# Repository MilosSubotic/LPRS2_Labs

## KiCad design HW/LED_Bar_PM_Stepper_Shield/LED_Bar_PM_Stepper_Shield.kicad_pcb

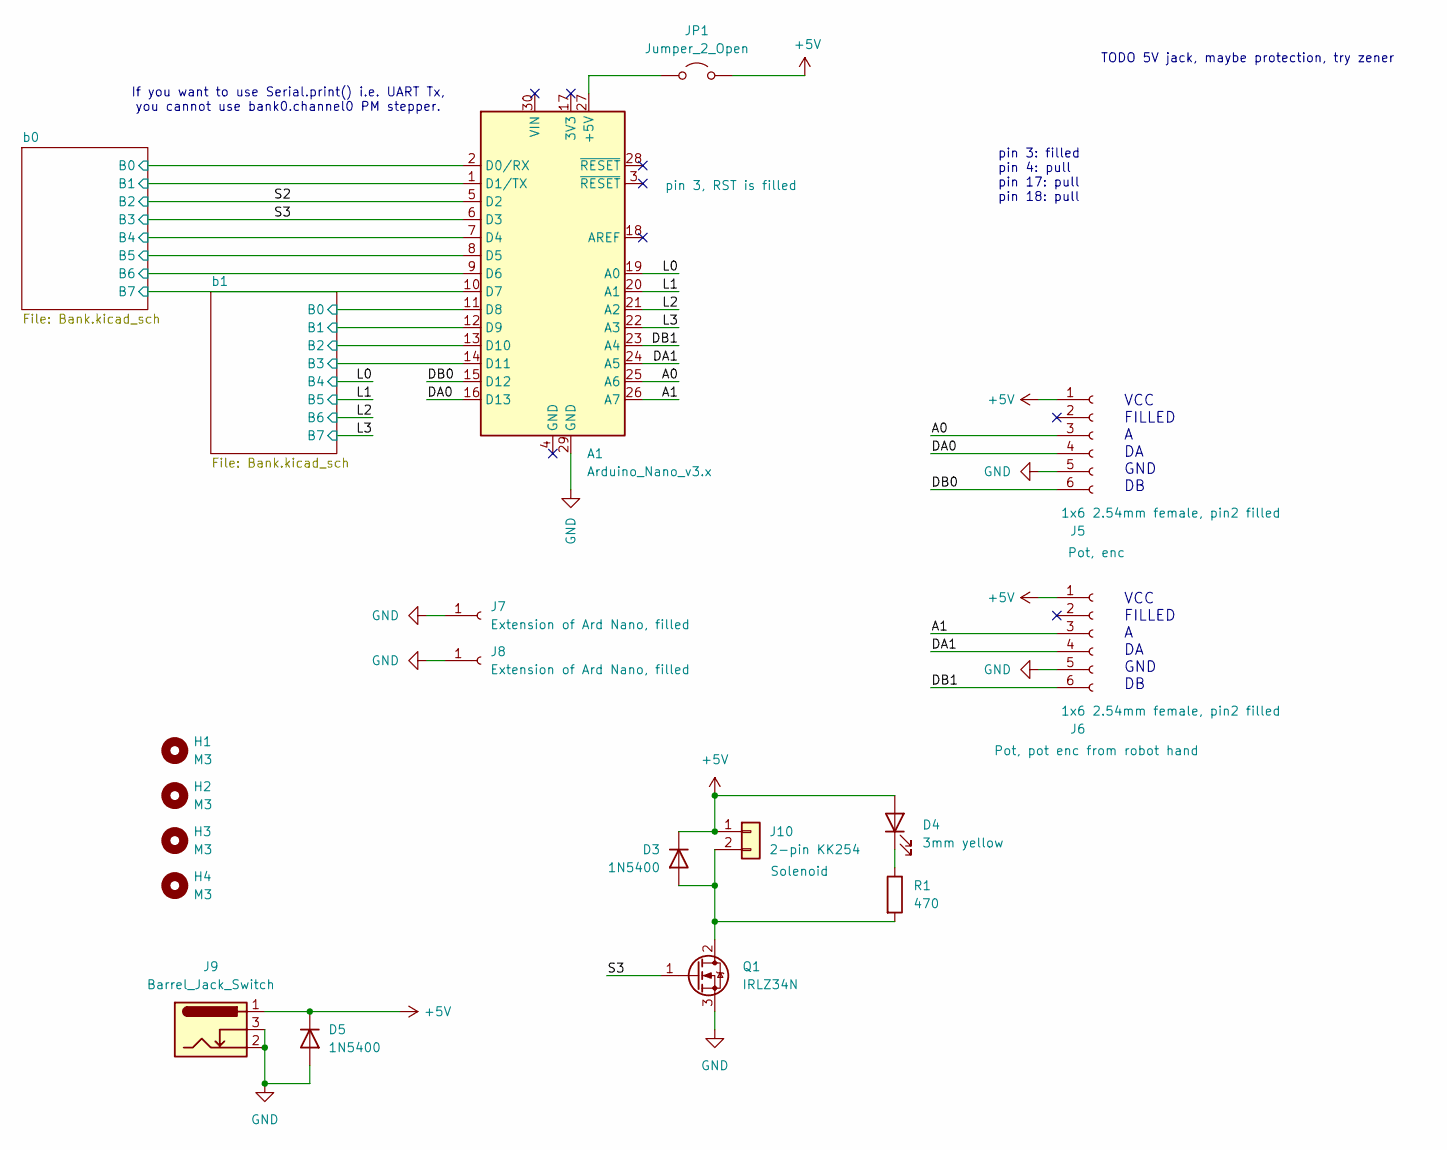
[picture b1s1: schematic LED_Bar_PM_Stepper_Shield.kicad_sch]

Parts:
A1: Arduino_Nano_v3.x; Arduino_Nano
D3, D5: 1N5400; D_DO-201AD_P5.08mm_Vertical_AnodeUp
D4: 3mm yellow; LED_D3.0mm_Pinf
H1, H2, H3, H4: M3; MountingHole_3.2mm_M3
J5, J6: 1x6 2.54mm female, pin2 filled; PinHeader_1x06_P2.54mm_Vertical
J7, J8: Extension of Ard Nano, filled; PinSocket_1x01_P2.54mm_Vertical
J9: Barrel_Jack_Switch; BarrelJack_Horizontal
J10: 2-pin KK254; Molex_KK-254_AE-6410-02A_1x02_P2.54mm_Vertical
JP1: Jumper_2_Open; PinHeader_1x02_P2.54mm_Vertical
Q1: IRLZ34N; TO-220-3_Vertical
R1: 470; R_Axial_DIN0207_L6.3mm_D2.5mm_P7.62mm_Horizontal

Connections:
+5V: D3.1 (K), D4.2 (A), D5.1 (K), J5.1, J6.1, J9.1, J10.1, JP1.2 (B); also elsewhere on the board
/A0: A1.25 (A6), J5.3
/A1: A1.26 (A7), J6.3
/DA0: A1.16 (D13), J5.4
/DA1: A1.24 (A5), J6.4
/DB0: A1.15 (D12), J5.6
/DB1: A1.23 (A4), J6.6
/L0: A1.19 (A0); also elsewhere on the board
/L1: A1.20 (A1); also elsewhere on the board
/L2: A1.21 (A2); also elsewhere on the board
/L3: A1.22 (A3); also elsewhere on the board
/S2: A1.5 (D2); also elsewhere on the board
/S3: A1.6 (D3), Q1.1 (G); also elsewhere on the board
/b0/B0: A1.2 (D0/RX); also elsewhere on the board
/b0/B1: A1.1 (D1/TX); also elsewhere on the board
/b0/B4: A1.7 (D4); also elsewhere on the board
/b0/B5: A1.8 (D5); also elsewhere on the board
/b0/B6: A1.9 (D6); also elsewhere on the board
/b0/B7: A1.10 (D7); also elsewhere on the board
/b1/B0: A1.11 (D8); also elsewhere on the board
/b1/B1: A1.12 (D9); also elsewhere on the board
/b1/B2: A1.13 (D10); also elsewhere on the board
/b1/B3: A1.14 (D11); also elsewhere on the board
GND: A1.29 (GND), D5.2 (A), J5.5, J6.5, J7.1, J8.1, J9.2, J9.3, Q1.3 (S); also elsewhere on the board
unnamed: A1.27 (+5V), JP1.1 (A)
unnamed: D3.2 (A), J10.2, Q1.2 (D), R1.2
unnamed: D4.1 (K), R1.1

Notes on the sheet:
If you want to use Serial.print() i.e. UART Tx, you cannot use bank0.channel0 PM stepper.
VCC FILLED A DA GND DB
TODO 5V jack, maybe protection, try zener
pin 3: filled pin 4: pull pin 17: pull pin 18: pull

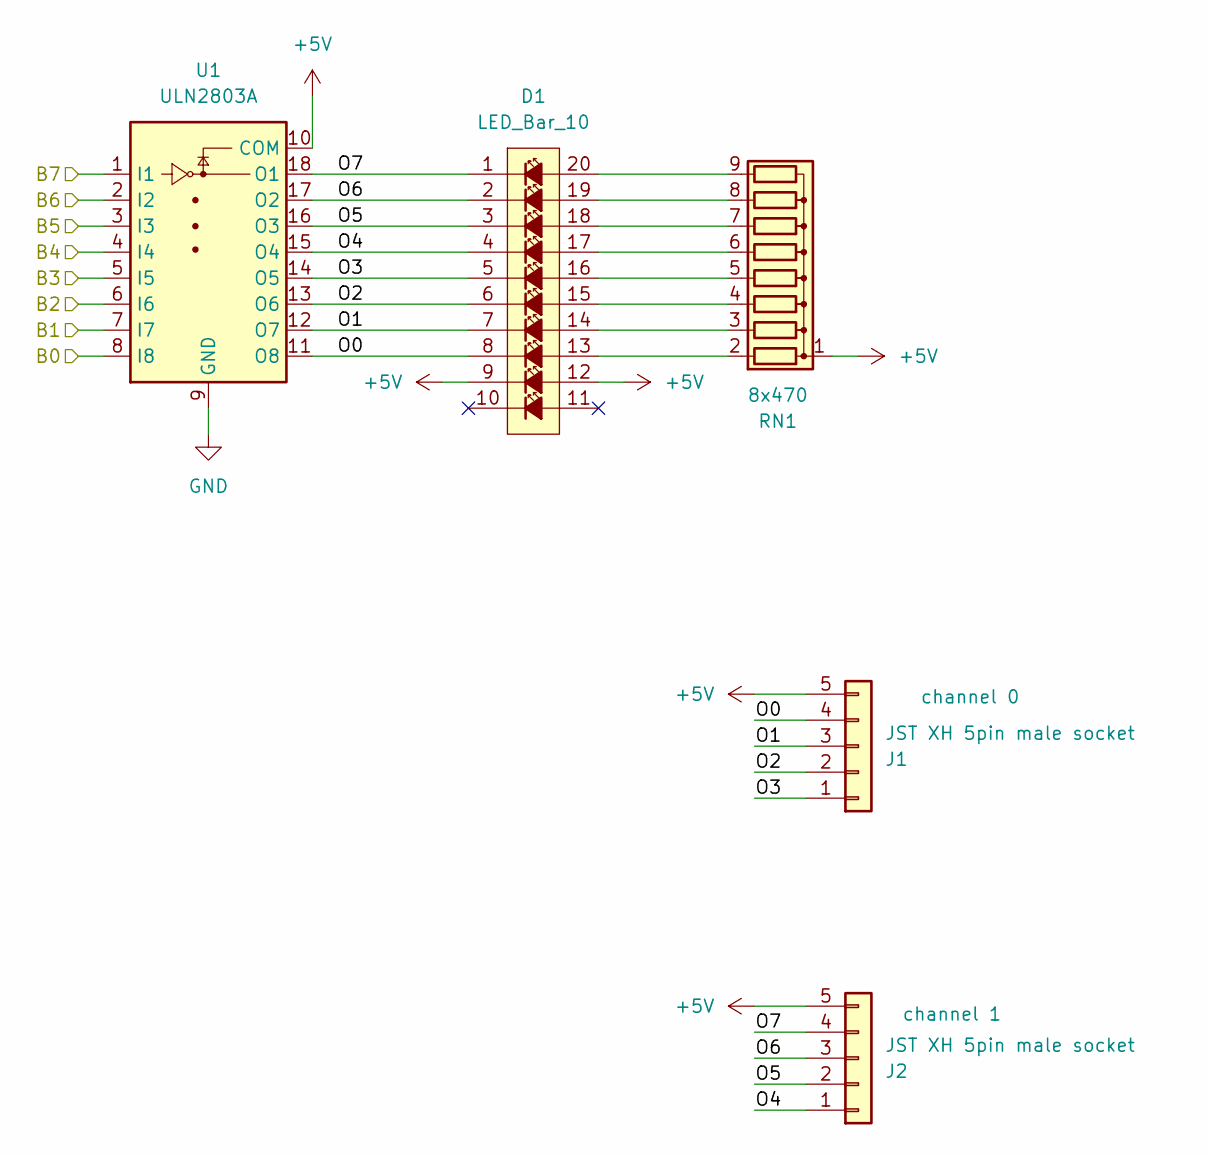
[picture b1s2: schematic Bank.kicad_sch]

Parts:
D1: LED_Bar_10; DIP-20_W7.62mm_Socket
J1, J2: JST XH 5pin male socket; JST_XH_B5B-XH-A_1x05_P2.50mm_Vertical
RN1: 8x470; R_Array_SIP9
U1: ULN2803A; DIP-18_W7.62mm_Socket

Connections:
+5V: D1.9, D1.12, J1.5, J2.5, RN1.1 (common), U1.10 (COM); also elsewhere on the board
/S2: U1.6 (I6); also elsewhere on the board
/S3: U1.5 (I5); also elsewhere on the board
/b0/B0: U1.8 (I8); also elsewhere on the board
/b0/B1: U1.7 (I7); also elsewhere on the board
/b0/B4: U1.4 (I4); also elsewhere on the board
/b0/B5: U1.3 (I3); also elsewhere on the board
/b0/B6: U1.2 (I2); also elsewhere on the board
/b0/B7: U1.1 (I1); also elsewhere on the board
/b0/O0: D1.8, J1.4, U1.11 (O8)
/b0/O1: D1.7, J1.3, U1.12 (O7)
/b0/O2: D1.6, J1.2, U1.13 (O6)
/b0/O3: D1.5, J1.1, U1.14 (O5)
/b0/O4: D1.4, J2.1, U1.15 (O4)
/b0/O5: D1.3, J2.2, U1.16 (O3)
/b0/O6: D1.2, J2.3, U1.17 (O2)
/b0/O7: D1.1, J2.4, U1.18 (O1)
GND: U1.9 (GND); also elsewhere on the board
unnamed: D1.13, RN1.2 (R1)
unnamed: D1.14, RN1.3 (R2)
unnamed: D1.15, RN1.4 (R3)
unnamed: D1.16, RN1.5 (R4)
unnamed: D1.17, RN1.6 (R5)
unnamed: D1.18, RN1.7 (R6)
unnamed: D1.19, RN1.8 (R7)
unnamed: D1.20, RN1.9 (R8)

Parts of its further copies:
D2: LED_Bar_10; DIP-20_W7.62mm_Socket
J3, J4: JST XH 5pin male socket; JST_XH_B5B-XH-A_1x05_P2.50mm_Vertical
RN2: 8x470; R_Array_SIP9
U2: ULN2803A; DIP-18_W7.62mm_Socket

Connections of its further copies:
+5V: D2.9, D2.12, J3.5, J4.5, RN2.1 (common), U2.10 (COM); also elsewhere on the board
/L0: U2.4 (I4); also elsewhere on the board
/L1: U2.3 (I3); also elsewhere on the board
/L2: U2.2 (I2); also elsewhere on the board
/L3: U2.1 (I1); also elsewhere on the board
/b1/B0: U2.8 (I8); also elsewhere on the board
/b1/B1: U2.7 (I7); also elsewhere on the board
/b1/B2: U2.6 (I6); also elsewhere on the board
/b1/B3: U2.5 (I5); also elsewhere on the board
/b1/O0: D2.8, J3.4, U2.11 (O8)
/b1/O1: D2.7, J3.3, U2.12 (O7)
/b1/O2: D2.6, J3.2, U2.13 (O6)
/b1/O3: D2.5, J3.1, U2.14 (O5)
/b1/O4: D2.4, J4.1, U2.15 (O4)
/b1/O5: D2.3, J4.2, U2.16 (O3)
/b1/O6: D2.2, J4.3, U2.17 (O2)
/b1/O7: D2.1, J4.4, U2.18 (O1)
GND: U2.9 (GND); also elsewhere on the board
unnamed: D2.13, RN2.2 (R1)
unnamed: D2.14, RN2.3 (R2)
unnamed: D2.15, RN2.4 (R3)
unnamed: D2.16, RN2.5 (R4)
unnamed: D2.17, RN2.6 (R5)
unnamed: D2.18, RN2.7 (R6)
unnamed: D2.19, RN2.8 (R7)
unnamed: D2.20, RN2.9 (R8)

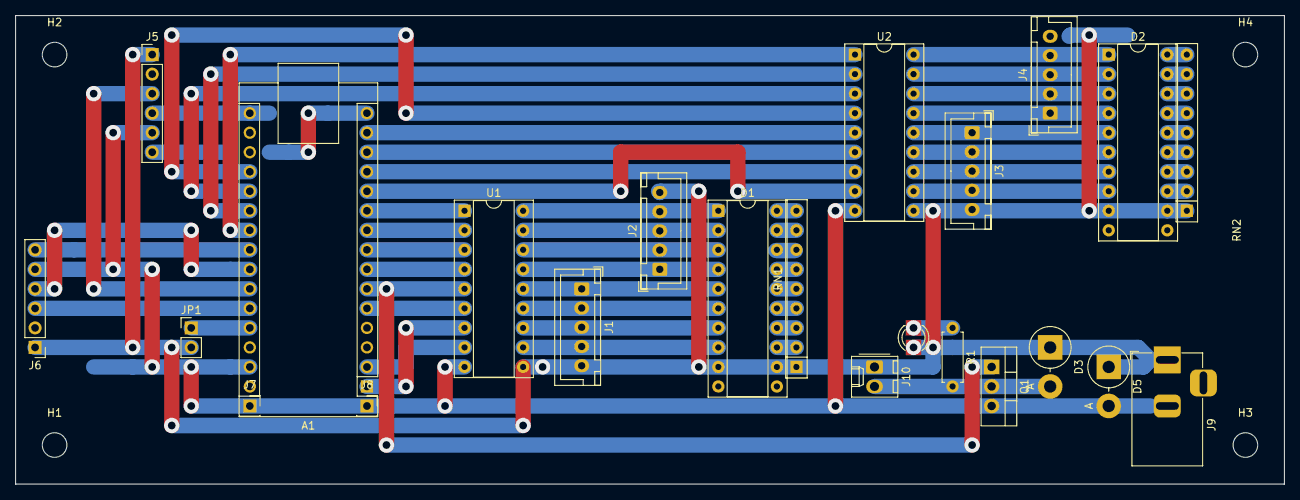
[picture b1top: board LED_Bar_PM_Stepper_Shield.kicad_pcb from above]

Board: 2 copper layers, 165.1 x 61.0 mm, 27 parts (0 on the bottom side), 59 nets.

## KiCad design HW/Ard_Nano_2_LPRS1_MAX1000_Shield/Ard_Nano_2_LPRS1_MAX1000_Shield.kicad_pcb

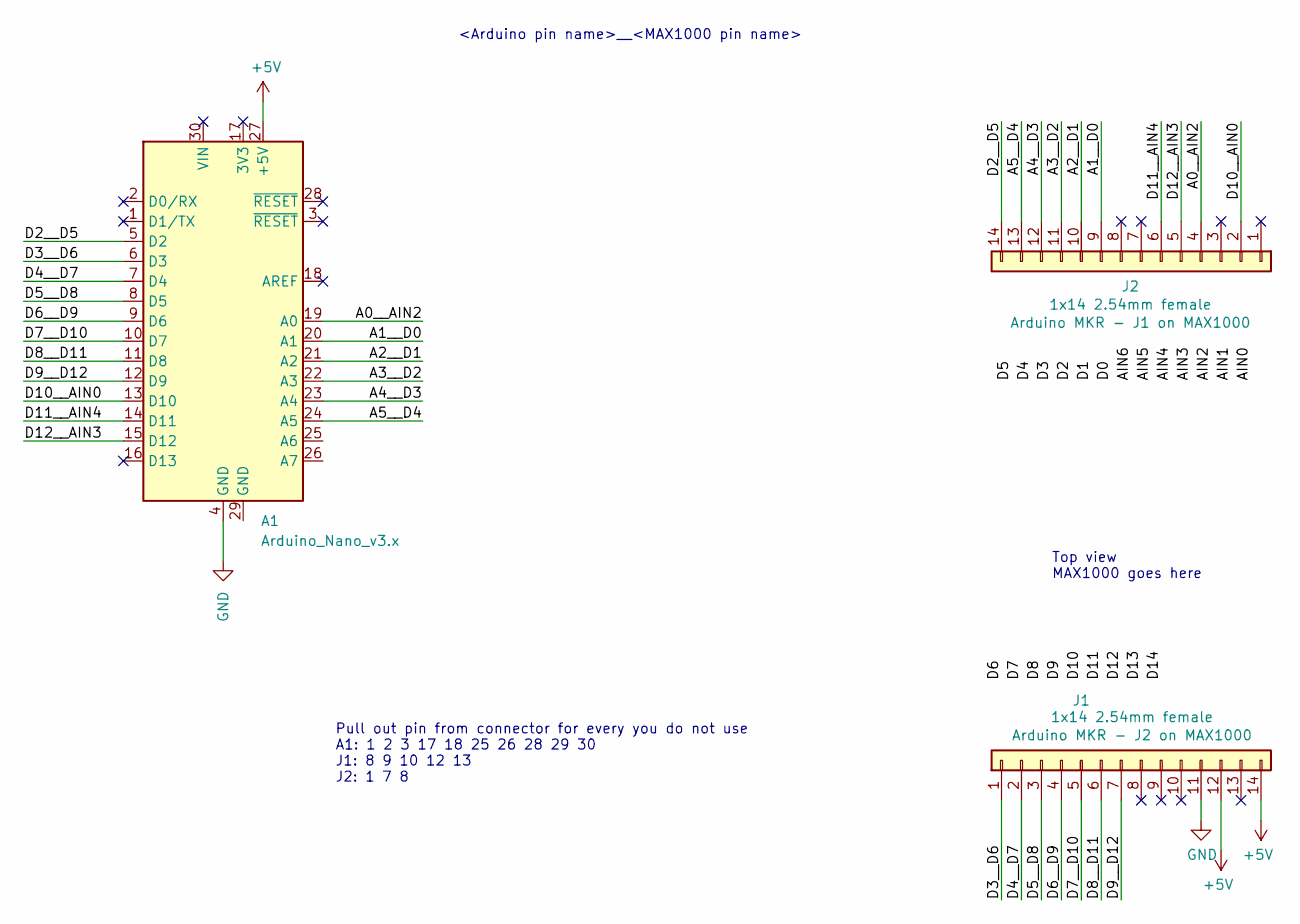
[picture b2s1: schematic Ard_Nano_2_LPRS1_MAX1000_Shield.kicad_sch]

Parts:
A1: Arduino_Nano_v3.x; Arduino_Nano
J1, J2: 1x14 2.54mm female; PinSocket_1x14_P2.54mm_Vertical

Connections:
+5V: A1.27 (+5V), J1.12, J1.14
/A0__AIN2: A1.19 (A0), J2.4
/A1__D0: A1.20 (A1), J2.9
/A2__D1: A1.21 (A2), J2.10
/A3__D2: A1.22 (A3), J2.11
/A4__D3: A1.23 (A4), J2.12
/A5__D4: A1.24 (A5), J2.13
/D2__D5: A1.5 (D2), J2.14
/D3__D6: A1.6 (D3), J1.1
/D4__D7: A1.7 (D4), J1.2
/D5__D8: A1.8 (D5), J1.3
/D6__D9: A1.9 (D6), J1.4
/D7__D10: A1.10 (D7), J1.5
/D8__D11: A1.11 (D8), J1.6
/D9__D12: A1.12 (D9), J1.7
/D10__AIN0: A1.13 (D10), J2.2
/D11__AIN4: A1.14 (D11), J2.6
/D12__AIN3: A1.15 (D12), J2.5
GND: A1.4 (GND), J1.11

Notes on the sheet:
Top view MAX1000 goes here
<Arduino pin name>__<MAX1000 pin name>
Pull out pin from connector for every you do not use A1: 1 2 3 17 18 25 26 28 29 30 J1: 8 9 10 12 13 J2: 1 7 8

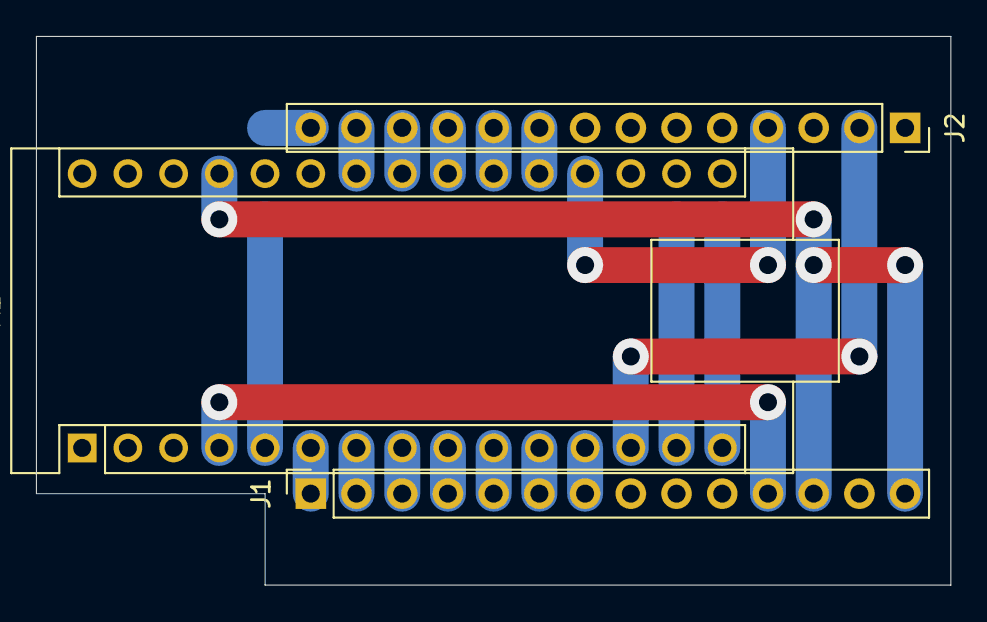
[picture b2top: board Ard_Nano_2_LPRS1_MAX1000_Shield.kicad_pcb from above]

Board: 2 copper layers, 50.8 x 30.5 mm, 3 parts (0 on the bottom side), 19 nets.

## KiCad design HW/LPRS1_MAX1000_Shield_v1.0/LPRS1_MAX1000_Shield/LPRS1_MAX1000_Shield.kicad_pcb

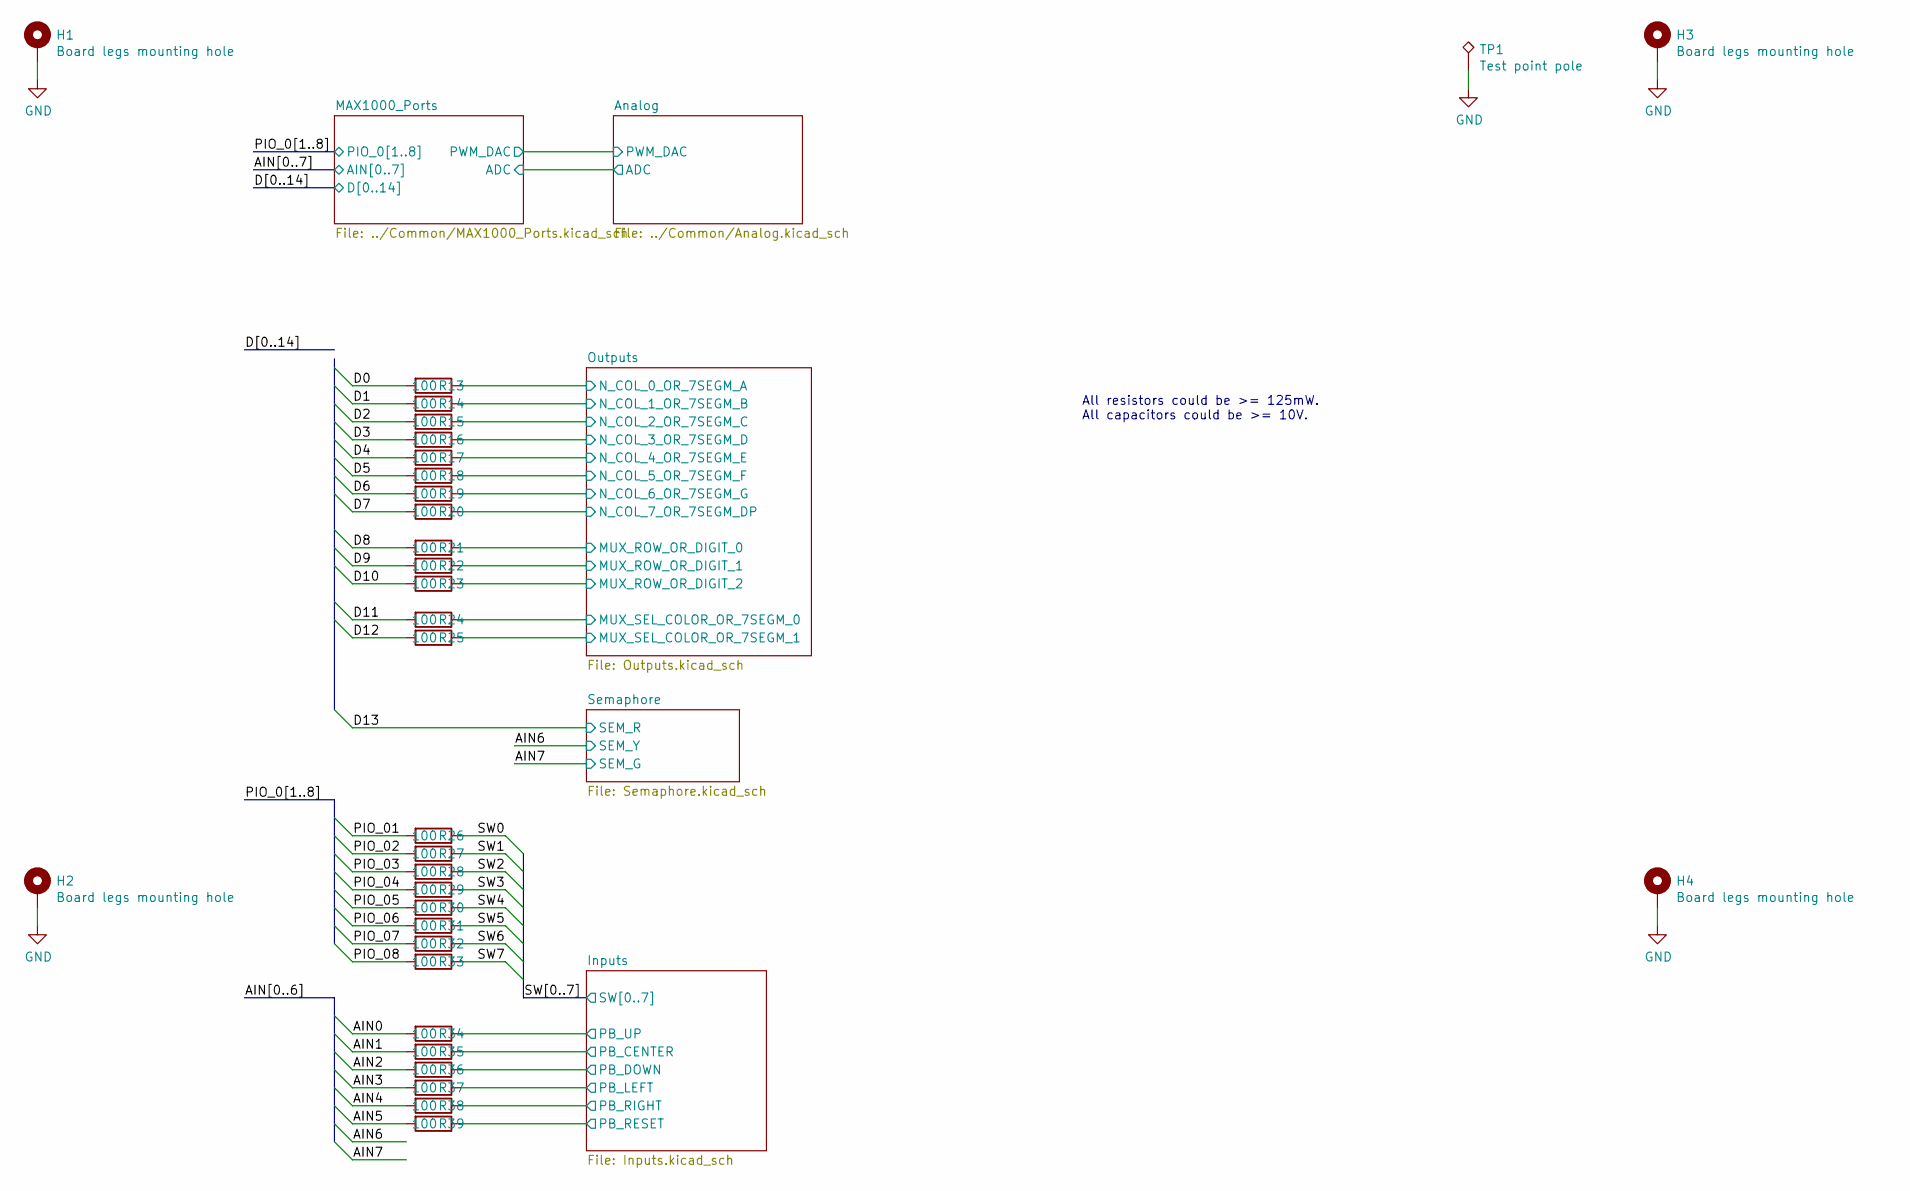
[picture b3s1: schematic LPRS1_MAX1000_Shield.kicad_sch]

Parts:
H1, H2, H3, H4: Board legs mounting hole; MountingHole_3.2mm_M3_Pad
R13, R14, R15, R16, R17, R18, R19, R20, R21, R22, R23, R24, R25, R26, R27, R28, R29, R30, R31, R32, R33, R34, R35, R36, R37, R38, R39: 100; R_0805_2012Metric_Pad1.15x1.40mm_HandSolder
TP1: Test point pole; PinHeader_1x01_P2.54mm_Vertical

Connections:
/AIN0: R34.2; also elsewhere on the board
/AIN1: R35.2; also elsewhere on the board
/AIN2: R36.2; also elsewhere on the board
/AIN3: R37.2; also elsewhere on the board
/AIN4: R38.2; also elsewhere on the board
/AIN5: R39.2; also elsewhere on the board
/D0: R13.2; also elsewhere on the board
/D1: R14.2; also elsewhere on the board
/D2: R15.2; also elsewhere on the board
/D3: R16.2; also elsewhere on the board
/D4: R17.2; also elsewhere on the board
/D5: R18.2; also elsewhere on the board
/D6: R19.2; also elsewhere on the board
/D7: R20.2; also elsewhere on the board
/D8: R21.2; also elsewhere on the board
/D9: R22.2; also elsewhere on the board
/D10: R23.2; also elsewhere on the board
/D11: R24.2; also elsewhere on the board
/D12: R25.2; also elsewhere on the board
/Inputs/PB_CENTER: R35.1; also elsewhere on the board
/Inputs/PB_DOWN: R36.1; also elsewhere on the board
/Inputs/PB_LEFT: R37.1; also elsewhere on the board
/Inputs/PB_RESET: R39.1; also elsewhere on the board
/Inputs/PB_RIGHT: R38.1; also elsewhere on the board
/Inputs/PB_UP: R34.1; also elsewhere on the board
/Outputs/MUX_ROW_OR_DIGIT_0: R21.1; also elsewhere on the board
/Outputs/MUX_ROW_OR_DIGIT_1: R22.1; also elsewhere on the board
/Outputs/MUX_ROW_OR_DIGIT_2: R23.1; also elsewhere on the board
/Outputs/MUX_SEL_COLOR_OR_7SEGM_0: R24.1; also elsewhere on the board
/Outputs/MUX_SEL_COLOR_OR_7SEGM_1: R25.1; also elsewhere on the board
/Outputs/N_COL_0_OR_7SEGM_A: R13.1; also elsewhere on the board
/Outputs/N_COL_1_OR_7SEGM_B: R14.1; also elsewhere on the board
/Outputs/N_COL_2_OR_7SEGM_C: R15.1; also elsewhere on the board
/Outputs/N_COL_3_OR_7SEGM_D: R16.1; also elsewhere on the board
/Outputs/N_COL_4_OR_7SEGM_E: R17.1; also elsewhere on the board
/Outputs/N_COL_5_OR_7SEGM_F: R18.1; also elsewhere on the board
/Outputs/N_COL_6_OR_7SEGM_G: R19.1; also elsewhere on the board
/Outputs/N_COL_7_OR_7SEGM_DP: R20.1; also elsewhere on the board
/PIO_01: R26.2; also elsewhere on the board
/PIO_02: R27.2; also elsewhere on the board
/PIO_03: R28.2; also elsewhere on the board
/PIO_04: R29.2; also elsewhere on the board
/PIO_05: R30.2; also elsewhere on the board
/PIO_06: R31.2; also elsewhere on the board
/PIO_07: R32.2; also elsewhere on the board
/PIO_08: R33.2; also elsewhere on the board
/SW0: R26.1; also elsewhere on the board
/SW1: R27.1; also elsewhere on the board
/SW2: R28.1; also elsewhere on the board
/SW3: R29.1; also elsewhere on the board
/SW4: R30.1; also elsewhere on the board
/SW5: R31.1; also elsewhere on the board
/SW6: R32.1; also elsewhere on the board
/SW7: R33.1; also elsewhere on the board
GND: H1.1, H2.1, H3.1, H4.1, TP1.1; also elsewhere on the board

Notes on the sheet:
All resistors could be >= 125mW. All capacitors could be >= 10V.

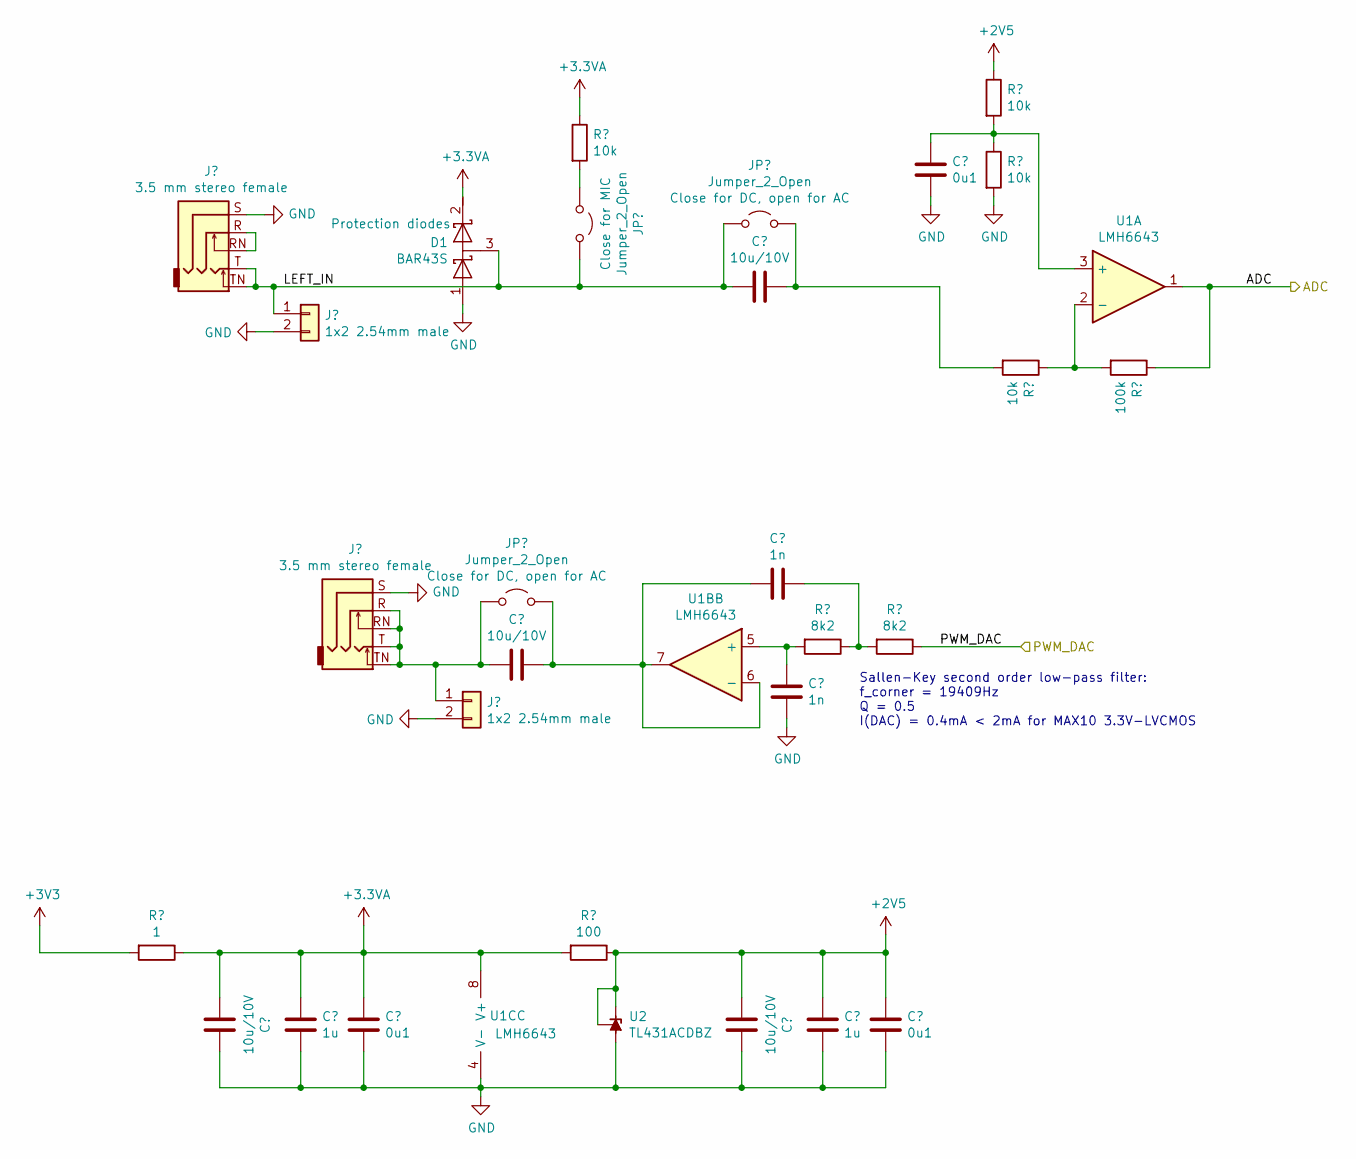
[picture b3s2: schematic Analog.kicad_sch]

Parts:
C1, C4, C5, C6: 10u/10V; C_1206_3216Metric_Pad1.42x1.75mm_HandSolder
C2, C9: 1u; C_0805_2012Metric_Pad1.15x1.40mm_HandSolder
C3, C10, C11: 0u1; C_0805_2012Metric_Pad1.15x1.40mm_HandSolder
C7, C8: 1n; C_0805_2012Metric_Pad1.15x1.40mm_HandSolder
D1: BAR43S; SOT-23
J6, J8: 3.5 mm stereo female; JC-128
J7, J9: 1x2 2.54mm male; PinHeader_1x02_P2.54mm_Vertical
JP1, JP2, JP3: Jumper_2_Open; PinHeader_1x02_P2.54mm_Vertical
R4: 1; R_0805_2012Metric_Pad1.15x1.40mm_HandSolder
R5, R9, R10, R11: 10k; R_0805_2012Metric_Pad1.15x1.40mm_HandSolder
R6: 100; R_0805_2012Metric_Pad1.15x1.40mm_HandSolder
R7, R8: 8k2; R_0805_2012Metric_Pad1.15x1.40mm_HandSolder
R12: 100k; R_0805_2012Metric_Pad1.15x1.40mm_HandSolder
U1, U1B, U1C: LMH6643; SOIC-8_3.9x4.9mm_P1.27mm
U2: TL431ACDBZ; SOT-23

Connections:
+2V5: C5.1, C9.1, C10.1, R6.1, R9.1, U2.1 (K), U2.2 (REF); also elsewhere on the board
+3.3VA: C1.1, C2.1, C3.1, D1.2 (K), R4.1, R5.1, R6.2, U1.8 (V+), U1C.8 (V+)
+3V3: R4.2; also elsewhere on the board
/Analog/ADC: R12.1, U1.1; also elsewhere on the board
/Analog/LEFT_IN: C6.1, D1.3 (common), J6.T, J6.TN, J7.1, JP2.2 (B), JP3.1 (A)
/Analog/PWM_DAC: R8.1; also elsewhere on the board
GND: C1.2, C2.2, C3.2, C5.2, C8.2, C9.2, C10.2, C11.2, D1.1 (A), J6.S, J7.2, J8.S, J9.2, R10.2, U1.4 (V-), U1C.4 (V-), U2.3 (A); also elsewhere on the board
unnamed: C4.1, J8.R, J8.RN, J8.T, J8.TN, J9.1, JP1.1 (A)
unnamed: C4.2, C7.2, JP1.2 (B), U1.6 (-), U1.7, U1B.6 (-), U1B.7
unnamed: C6.2, JP3.2 (B), R11.2
unnamed: C7.1, R7.1, R8.2
unnamed: C8.1, R7.2, U1.5 (+), U1B.5 (+)
unnamed: C11.1, R9.2, R10.1, U1.3 (+)
unnamed: J6.R, J6.RN
unnamed: JP2.1 (A), R5.2
unnamed: R11.1, R12.2, U1.2 (-)

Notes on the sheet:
Sallen-Key second order low-pass filter: f_corner = 19409Hz Q = 0.5 I(DAC) = 0.4mA < 2mA for MAX10 3.3V-LVCMOS

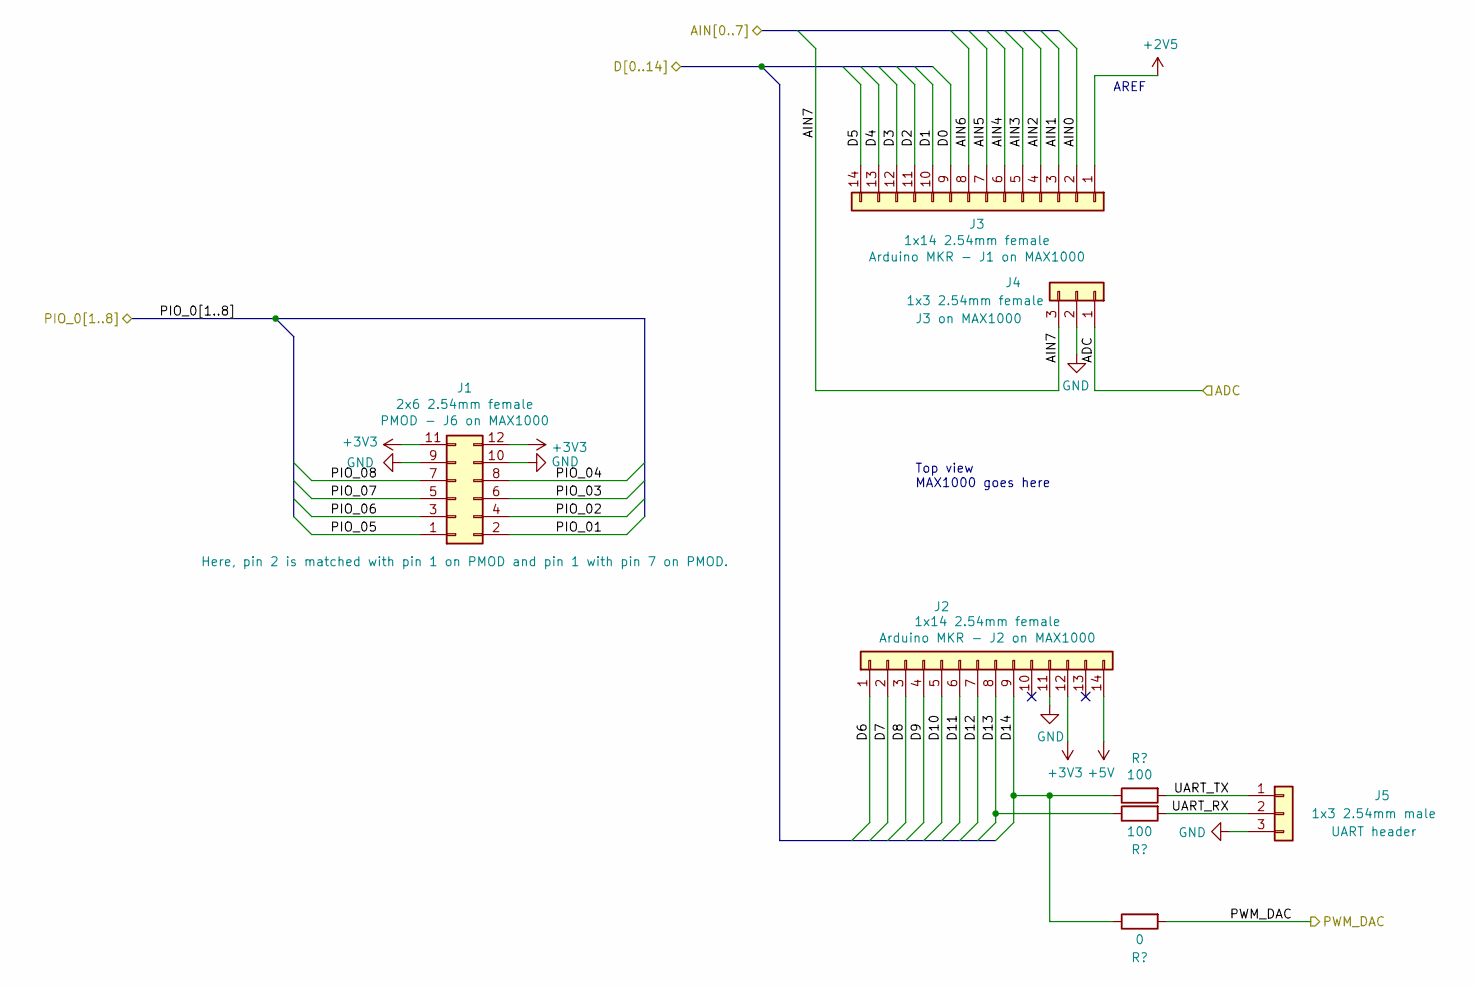
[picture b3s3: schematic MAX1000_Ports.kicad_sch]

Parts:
J1: 2x6 2.54mm female; PinSocket_2x06_P2.54mm_Vertical
J2, J3: 1x14 2.54mm female; PinSocket_1x14_P2.54mm_Vertical
J4: 1x3 2.54mm female; PinSocket_1x03_P2.54mm_Vertical
J5: 1x3 2.54mm male; PinHeader_1x03_P2.54mm_Vertical
R1, R2: 100; R_0805_2012Metric_Pad1.15x1.40mm_HandSolder
R3: 0; R_0805_2012Metric_Pad1.15x1.40mm_HandSolder

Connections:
+2V5: J3.1; also elsewhere on the board
+3V3: J1.11, J1.12, J2.12; also elsewhere on the board
+5V: J2.14; also elsewhere on the board
/AIN0: J3.2; also elsewhere on the board
/AIN1: J3.3; also elsewhere on the board
/AIN2: J3.4; also elsewhere on the board
/AIN3: J3.5; also elsewhere on the board
/AIN4: J3.6; also elsewhere on the board
/AIN5: J3.7; also elsewhere on the board
/AIN6: J3.8; also elsewhere on the board
/AIN7: J4.3; also elsewhere on the board
/Analog/ADC: J4.1; also elsewhere on the board
/Analog/PWM_DAC: R3.2; also elsewhere on the board
/D0: J3.9; also elsewhere on the board
/D1: J3.10; also elsewhere on the board
/D2: J3.11; also elsewhere on the board
/D3: J3.12; also elsewhere on the board
/D4: J3.13; also elsewhere on the board
/D5: J3.14; also elsewhere on the board
/D6: J2.1; also elsewhere on the board
/D7: J2.2; also elsewhere on the board
/D8: J2.3; also elsewhere on the board
/D9: J2.4; also elsewhere on the board
/D10: J2.5; also elsewhere on the board
/D11: J2.6; also elsewhere on the board
/D12: J2.7; also elsewhere on the board
/D13: J2.8, R2.1; also elsewhere on the board
/MAX1000_Ports/D14: J2.9, R1.1, R3.1
/MAX1000_Ports/UART_RX: J5.2, R2.2
/MAX1000_Ports/UART_TX: J5.1, R1.2
/PIO_01: J1.2; also elsewhere on the board
/PIO_02: J1.4; also elsewhere on the board
/PIO_03: J1.6; also elsewhere on the board
/PIO_04: J1.8; also elsewhere on the board
/PIO_05: J1.1; also elsewhere on the board
/PIO_06: J1.3; also elsewhere on the board
/PIO_07: J1.5; also elsewhere on the board
/PIO_08: J1.7; also elsewhere on the board
GND: J1.9, J1.10, J2.11, J4.2, J5.3; also elsewhere on the board

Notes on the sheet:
AREF
Top view MAX1000 goes here
